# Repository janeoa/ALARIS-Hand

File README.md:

# ALARIS Hand control project
## Credits
This is an ALARIS project supervised by 

* Almas Shintemirov
* Artemiy Oleinikov
* Ayaulym Nurpeissova
* Nurzhan Yesmagambet
* Anton Kim

## Used tools
* 3D printer
* Arduino
* motors
* STM32

## PCB on EAGLE

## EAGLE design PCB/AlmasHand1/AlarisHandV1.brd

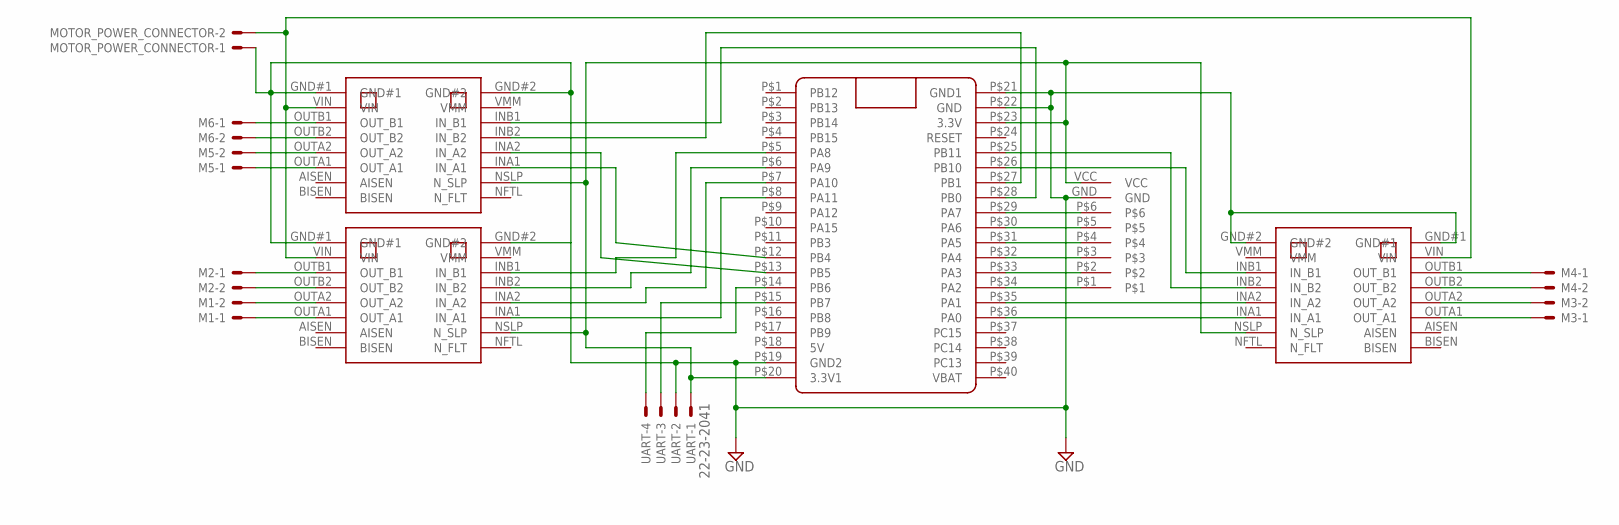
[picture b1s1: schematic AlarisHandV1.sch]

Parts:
M1, M2, M3, M4, M5, M6: 22-23-2021
MOTOR_POWER_CONNECTOR: 22-23-2021
U$1, U$2, U$3: POLOLUDRV8833
U$4: BLUE_PILL
U$5: SENSOR_RAIL
UART: 22-23-2041

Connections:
3.3V: U$1.NSLP (N_SLP), U$2.NSLP (N_SLP), U$3.NSLP (N_SLP), U$4.P$20 (3.3V1), U$4.P$23 (3.3V), U$5.VCC, UART.1
GND: MOTOR_POWER_CONNECTOR.1, U$1.GND#1, U$1.GND#2, U$2.GND#1, U$2.GND#2, U$3.GND#1, U$3.GND#2, U$4.P$19 (GND2), U$4.P$21 (GND1), U$4.P$22 (GND), U$5.GND, UART.2
M1A: M1.1, U$1.OUTA1 (OUT_A1)
M1B: M1.2, U$1.OUTA2 (OUT_A2)
M2A: M2.1, U$1.OUTB1 (OUT_B1)
M2B: M2.2, U$1.OUTB2 (OUT_B2)
M3A: M3.1, U$3.OUTA1 (OUT_A1)
M3B: M3.2, U$3.OUTA2 (OUT_A2)
M4A: M4.1, U$3.OUTB1 (OUT_B1)
M4B: M4.2, U$3.OUTB2 (OUT_B2)
M5A: M5.1, U$2.OUTA1 (OUT_A1)
M5B: M5.2, U$2.OUTA2 (OUT_A2)
M6A: M6.1, U$2.OUTB1 (OUT_B1)
M6B: M6.2, U$2.OUTB2 (OUT_B2)
MOTOR_POWER: MOTOR_POWER_CONNECTOR.2, U$1.VIN, U$2.VIN, U$3.VIN
unnamed: U$4.P$14 (PB6), UART.4
unnamed: U$1.INA1 (IN_A1), U$4.P$8 (PA11)
unnamed: U$1.INA2 (IN_A2), U$4.P$7 (PA10)
unnamed: U$1.INB2 (IN_B2), U$4.P$6 (PA9)
unnamed: U$3.INB2 (IN_B2), U$4.P$25 (PB11)
unnamed: U$3.INB1 (IN_B1), U$4.P$26 (PB10)
unnamed: U$3.INA2 (IN_A2), U$4.P$35 (PA1)
unnamed: U$3.INA1 (IN_A1), U$4.P$36 (PA0)
unnamed: U$1.INB1 (IN_B1), U$4.P$5 (PA8)
unnamed: U$4.P$34 (PA2), U$5.P$1
unnamed: U$4.P$29 (PA7), U$5.P$6
unnamed: U$4.P$30 (PA6), U$5.P$5
unnamed: U$4.P$31 (PA5), U$5.P$4
unnamed: U$4.P$32 (PA4), U$5.P$3
unnamed: U$4.P$33 (PA3), U$5.P$2
unnamed: U$2.INA1 (IN_A1), U$4.P$12 (PB4)
unnamed: U$2.INA2 (IN_A2), U$4.P$13 (PB5)
unnamed: U$2.INB1 (IN_B1), U$4.P$28 (PB0)
unnamed: U$2.INB2 (IN_B2), U$4.P$27 (PB1)
UART_RX: U$4.P$15 (PB7), UART.3

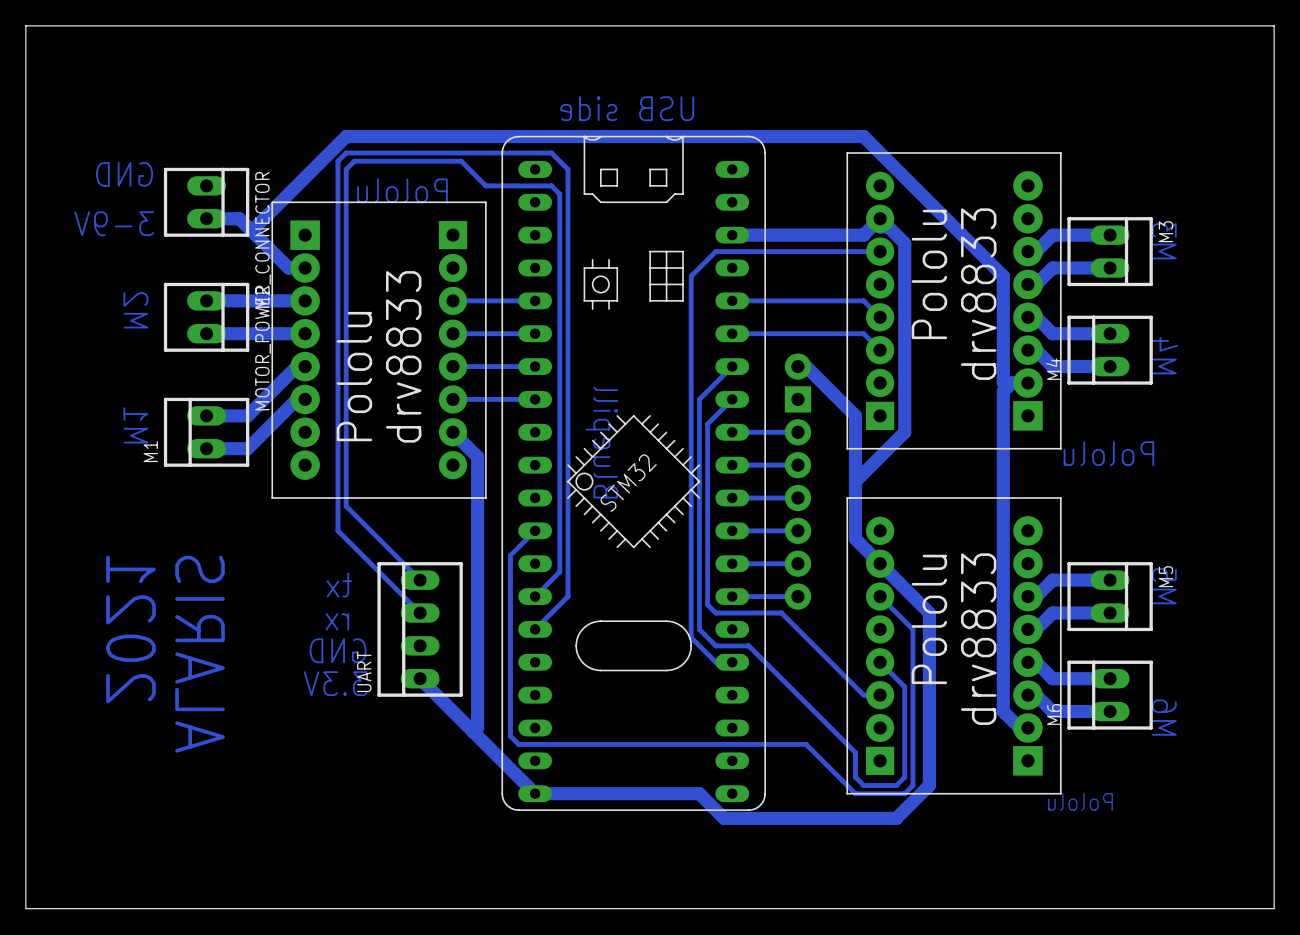
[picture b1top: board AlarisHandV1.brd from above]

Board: 2 copper layers, 96.5 x 68.2 mm, 13 parts (0 on the bottom side), 35 nets.

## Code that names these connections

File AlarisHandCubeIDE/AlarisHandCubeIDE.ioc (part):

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Mcu.Name=STM32F103C(4-6)Tx
Mcu.Package=LQFP48
Mcu.UserName=STM32F103C6Tx
PA0-WKUP.GPIOParameters=GPIO_Label
PA0-WKUP.GPIO_Label=M3A
PA0-WKUP.Signal=S_TIM2_CH1_ETR
PA1.GPIOParameters=GPIO_Label
PA1.GPIO_Label=M3B
PA1.Signal=S_TIM2_CH2
PA10.GPIOParameters=GPIO_Label
PA10.GPIO_Label=M2A
PA10.Signal=S_TIM1_CH3
PA11.GPIOParameters=GPIO_Label
PA11.GPIO_Label=M2B
PA11.Signal=S_TIM1_CH4
PA13.Mode=Trace_Asynchronous_SW
PA13.Signal=SYS_JTMS-SWDIO
PA14.Mode=Trace_Asynchronous_SW
PA14.Signal=SYS_JTCK-SWCLK
PA2.GPIOParameters=GPIO_Label
PA2.GPIO_Label=pot1
PA2.Signal=ADCx_IN2
PA3.GPIOParameters=GPIO_Label
PA3.GPIO_Label=pot2
PA3.Signal=ADCx_IN3
PA4.GPIOParameters=GPIO_Label
PA4.GPIO_Label=pot3
PA4.Signal=ADCx_IN4
PA5.GPIOParameters=GPIO_Label
PA5.GPIO_Label=pot4
PA5.Signal=ADCx_IN5
PA6.GPIOParameters=GPIO_Label
PA6.GPIO_Label=pot5
PA6.Signal=ADCx_IN6
PA7.GPIOParameters=GPIO_Label
PA7.GPIO_Label=pot6
PA7.Signal=ADCx_IN7
PA8.GPIOParameters=GPIO_Label
PA8.GPIO_Label=M1A
PA8.Signal=S_TIM1_CH1
PA9.GPIOParameters=GPIO_Label
PA9.GPIO_Label=M1B
PA9.Signal=S_TIM1_CH2
PB0.GPIOParameters=GPIO_Label
PB0.GPIO_Label=M6A
PB0.Signal=S_TIM3_CH3
PB1.GPIOParameters=GPIO_Label
PB1.GPIO_Label=M6B
PB1.Signal=S_TIM3_CH4
PB10.GPIOParameters=GPIO_Label
PB10.GPIO_Label=M4A
PB10.Signal=S_TIM2_CH3
PB11.GPIOParameters=GPIO_Label
PB11.GPIO_Label=M4B
PB11.Signal=S_TIM2_CH4
PB3.Mode=Trace_Asynchronous_SW
PB3.Signal=SYS_JTDO-TRACESWO
PB4.GPIOParameters=GPIO_Label
PB4.GPIO_Label=M5A
PB4.Signal=S_TIM3_CH1
PB5.GPIOParameters=GPIO_Label
PB5.GPIO_Label=M5B
PB5.Signal=S_TIM3_CH2
PB6.Mode=Asynchronous
PB6.Signal=USART1_TX
PB7.Mode=Asynchronous
PB7.Signal=USART1_RX
PC13-TAMPER-RTC.Signal=GPIO_Output
PC14-OSC32_IN.Mode=LSE-External-Oscillator
PC14-OSC32_IN.Signal=RCC_OSC32_IN
PC15-OSC32_OUT.Mode=LSE-External-Oscillator
PC15-OSC32_OUT.Signal=RCC_OSC32_OUT
PD0-OSC_IN.Mode=HSE-External-Oscillator
PD0-OSC_IN.Signal=RCC_OSC_IN
PD1-OSC_OUT.Mode=HSE-External-Oscillator
PD1-OSC_OUT.Signal=RCC_OSC_OUT
RCC.SYSCLKFreq_VALUE=72000000
RCC.SYSCLKSource=RCC_SYSCLKSOURCE_PLLCLK
board=custom

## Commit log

2021-05-11 init
2021-05-11 Motor class
2021-05-11 README
2021-05-11 gitignore
2021-05-12 support for nucleo
2021-05-12 tried libopencm3 discarded due to manual adc config
2021-05-12 gitignore EAGLE
2021-05-12 STM32CubeIDE pins assigned
2021-05-13 cleanup
2021-05-13 copy working PCB layout to the GIT
2021-05-13 .gitignore +DS_Store
2021-05-13 untrack DS_Store
2021-05-13 updates on board
2021-05-14 Gerber generation
2021-05-14 Updated PCB drills for printing
2021-05-14 converted CubeIDE to cpp
2021-05-14 pcb image for README
2021-05-14 ADC and Motor class
2021-05-17 no PID reference movement
2021-05-18 fixed M1 port connection
2021-05-18 PWM enabled
2021-05-18 logged data for PID
2021-05-19 added last 5 steps with tolerance check for moving
2021-05-20 stopping in 60 cycles
2021-05-20 struggle with DMA
2021-05-21 cleanup the CAM PCB files
2021-05-21 logging stalling
2021-05-21 open/close with stalling
2021-11-01 new gitignore for C/C++ and Eclipse
2021-11-01 before adding EasyTransfer
